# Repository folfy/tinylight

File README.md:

tinylight
=========

USB client for prismatik and tinylight host

Inexpensive USB Light-pack client, based on an Atmel xMega Controller.
Intended for LED Strips based on the WS2801 IC.<br>
<br>
<b>Features:</b>
- On-chip USB interface
- RGB status led
- Supply current and voltage measurement
- 6 GPIO solderpads
- PDI programming interface

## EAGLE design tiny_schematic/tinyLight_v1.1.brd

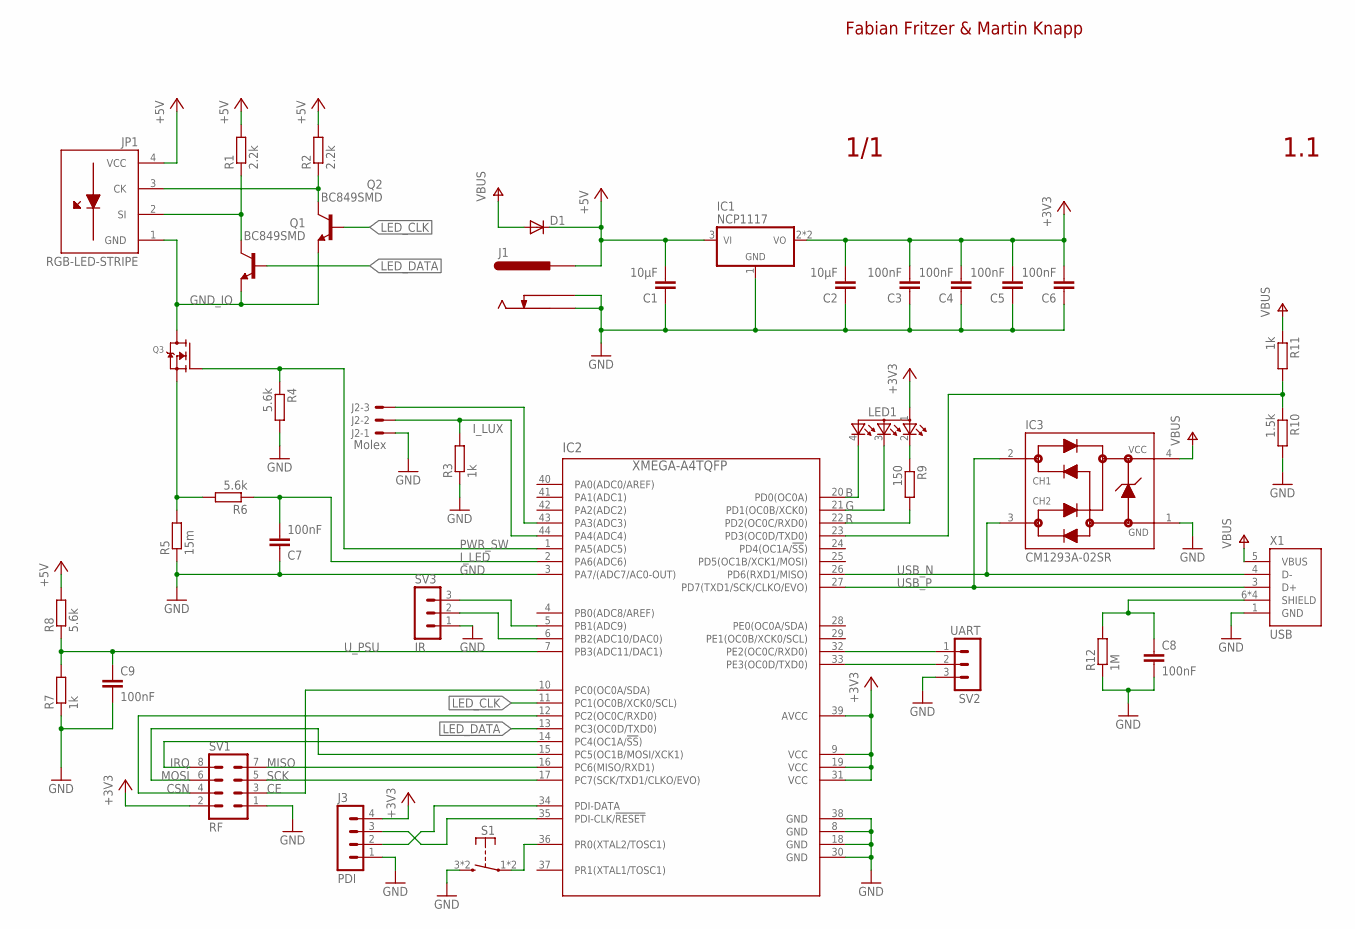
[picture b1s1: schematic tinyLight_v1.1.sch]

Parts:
C1, C2: 10µF; C2012
C3, C4, C5, C6, C7, C8, C9: 100nF; C2012
D1: DIODE-DO-214AC; DO-214AC
IC1: NCP1117; SOT223
IC2: XMEGA-A4TQFP; TQFP44
IC3: CM1293A-02SR; SOT143
J1: RASM722PX
J2: Molex; 6410-03
J3: PDI; MA04-1
JP1: RGB-LED-STRIPE; LED-STRIPE
LED1: RGB-LEDMINI; P-LCC-4_M
Q1, Q2: BC849SMD; SOT23-BEC
Q3: MOSFET-N; SOT457R_PHILIPS
R1, R2: 2.2k; M2012
R3, R7, R11: 1k; M2012
R4, R6, R8: 5.6k; M2012
R5: 15m; M3216
R9: 150; M2012
R10: 1.5k; M2012
R12: 1M; M2012
S1: SPST_PB; LSH_6X6
SV1: RF; MA04-2
SV2: UART; MA03-1
SV3: IR; MA03-1
X1: MICRO-USB; MIKRO_B

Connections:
+3V3: C2.2, C3.2, C4.2, C5.2, C6.2, IC1.2 (VOUT), IC1.T (VOUT), IC2.9 (VCC), IC2.19 (VCC), IC2.31 (VCC), IC2.39 (AVCC), J3.4, LED1.1 (ANODE), SV1.2
+5V: C1.2, D1.C, IC1.3 (VIN), J1.TIP, JP1.4 (VCC), R1.2, R2.2, R8.2
B: IC2.20 (PD0(OC0A)), LED1.4 (CBLUE)
CE: IC2.10 (PC0(OC0A/SDA)), SV1.3
CK: JP1.3 (CK), Q2.C, R2.1
CSN: IC2.12 (PC2(OC0C/RXD0)), SV1.4
DATA: JP1.2 (SI), Q1.C, R1.1
G: IC2.21 (PD1(OC0B/XCK0)), LED1.3 (CGREEN)
GND: C1.1, C2.1, C3.1, C4.1, C5.1, C6.1, C7.1, C8.2, C9.2, IC1.1 (GND), IC2.3 (PA7/(ADC7/AC0-OUT)), IC2.8 (GND), IC2.18 (GND), IC2.30 (GND), IC2.38 (GND), IC3.1 (GND), J1.SHUNT, J1.SLEEVE (SLEVE), J2.1, J3.1, R3.1, R4.2, R5.1, R7.1, R10.2, R12.1, S1.3 (2), S1.4 (2), SV1.1, SV2.3, SV3.1, X1.1 (GND)
GND_IO: JP1.1 (GND), Q1.E, Q2.E, Q3.1 (D), Q3.2 (D), Q3.5 (D), Q3.6 (D)
IRQ: IC2.14 (PC4(OC1A/!SS!)), SV1.8
I_LED: C7.2, IC2.2 (PA6(ADC6)), R6.1
I_LUX: IC2.44 (PA4(ADC4)), J2.2, R3.2
LED_CLK: IC2.11 (PC1(OC0B/XCK0/SCL)), Q2.B
LED_DATA: IC2.13 (PC3(OC0D/TXD0)), Q1.B
LED_R: LED1.2 (CRED), R9.1
MISO: IC2.16 (PC6(MISO/RXD1)), SV1.7
MOSI: IC2.15 (PC5(OC1B/MOSI/XCK1)), SV1.6
unnamed: IC2.6 (PB2(ADC10/DAC0)), SV3.2
unnamed: IC2.43 (PA3(ADC3)), J2.3
unnamed: IC2.33 (PE3(OC0D/TXD0)), SV2.2
unnamed: IC2.32 (PE2(OC0C/RXD0)), SV2.1
unnamed: IC2.36 (PR0(XTAL2/TOSC1)), S1.1, S1.2 (1)
unnamed: IC2.35 (PDI-CLK/!RESET), J3.3
unnamed: IC2.34 (PDI-DATA), J3.2
unnamed: IC2.5 (PB1(ADC9)), SV3.3
PWR_SW: IC2.1 (PA5(ADC5)), Q3.3 (G), R4.1
R: IC2.22 (PD2(OC0C/RXD0)), R9.2
SCK: IC2.17 (PC7(SCK/TXD1/CLKO/EVO)), SV1.5
SHIELD: C8.1, R12.2, X1.6 (SHIELD), X1.7 (SHIELD), X1.8 (SHIELD), X1.9 (SHIELD)
USB_N: IC2.26 (PD6(RXD1/MISO)), IC3.3 (CH2), X1.4 (D-)
USB_P: IC2.27 (PD7(TXD1/SCK/CLKO/EVO)), IC3.2 (CH1), X1.3 (D+)
U_PSU: C9.1, IC2.7 (PB3(ADC11/DAC1)), R7.2, R8.1
VBUS: D1.A, IC3.4 (VCC), R11.1, X1.5 (VBUS)
VBUS_LOW: IC2.23 (PD3(OC0D/TXD0)), R10.1, R11.2
VGND: Q3.4 (S), R5.2, R6.2

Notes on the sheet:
1.1
1/1
Fabian Fritzer & Martin Knapp

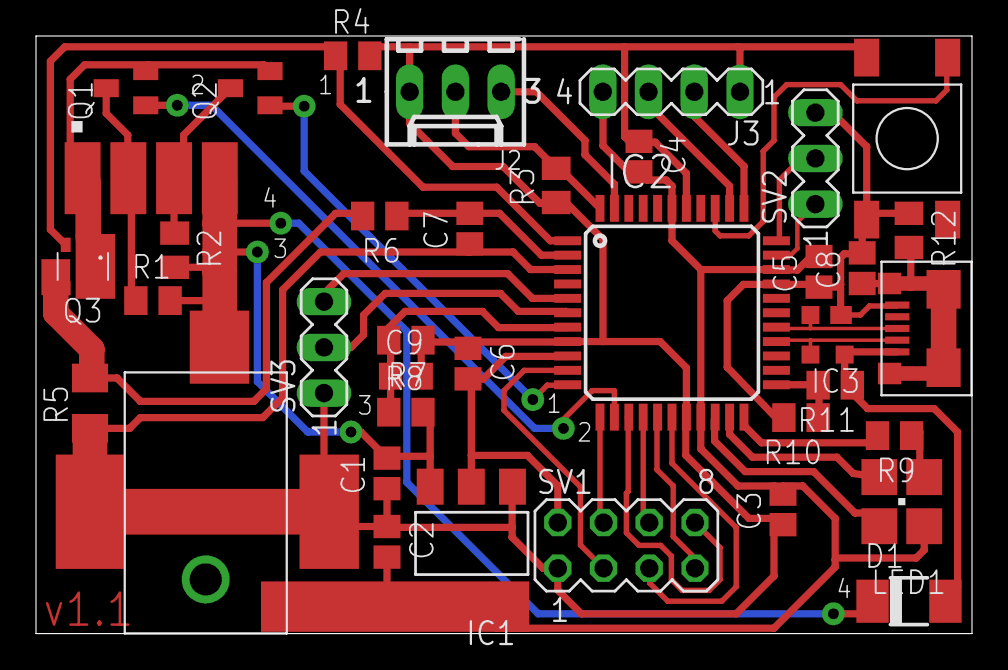
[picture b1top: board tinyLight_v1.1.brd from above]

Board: 2 copper layers, 52.0 x 33.2 mm, 39 parts (0 on the bottom side), 36 nets.

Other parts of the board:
U$1: OSHW_8X100_NOTEXT

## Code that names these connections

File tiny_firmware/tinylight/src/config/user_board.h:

/**
 * \file
 *
 * \brief User board definition template
 *
 * I/O Pins:
 *	PA1:	A_IN:		Light Sensor
 *	PA5:	D_OUT:		Power Mosfet
 *	PA6:	A_IN:		Current-Sensor +
 *	PA7:	A_IN:		Current-Sensor -
 *	PB1:	D_OUT:		IR_enable
 *	PB2:	D_IN:		IR-In
 *	PB3:	A_IN:		+5V-Sensor
 *	PC1:	D_OUT:		XCK-Led Stripe
 *	PC3:	D_OUT:		TX-Led Stripe
 *	PD0:	D_OUT:		Led blue
 *	PD1:	D_OUT:		Led green
 *	PD2:	D_OUT:		Led red
 *	PD3:	D_IN:		USB VBus Detection
 *	PD6:	D_INOUT:	USB Data -
 *	PD7:	D_INOUT:	USB Data +
 *  PE1:    D_OUT:      LED Data - clock (WS2811/WS2812)
 *  PE3:    D_OUT:      LED Data - data  (WS2811/WS2812)
 *	PR3:	D_IN:		Pushbutton
 *
 * Timer/counter units:
 *  TCC0:   LED (WS2811/WS2812)
 *  TCC1:	IR
 *	TCD0:	PWM Status LED
 *	TCD1:	DMA-Wait
 *
 * Event channels:
 *  EVCH0:  ADC
 *  EVCH1:  LED_CLK			(CLK, Falling edge)
 *  EVCH2:  LED_DATA		(DATA, both edges)
 *
 * DMA channels:
 *  DMACH0:	LED Timer
 *  DMACH1: LED Data
 */

 /* This file is intended to contain definitions and configuration details for
 * features and devices that are available on the board, e.g., frequency and
 * startup time for an external crystal, external memory devices, LED and USART
 * pins.
 */

#ifndef USER_BOARD_H
#define USER_BOARD_H

#include <conf_board.h>

//#define BOARD_REV 0x01			//prototype / debug board
//#define BOARD_REV 0x10			//first release
#define BOARD_REV 0x11			//reduced LED pull-up resistor value
/*	uncomment definition to select expected (wireless) module on expansion header	*/
#define RF_avail 1  			//RF-Transceiver
//#define RF_avail 2  			//BT-Transceiver
//#define RF_avail 3  			//Debug Output (remove RF module first!)
//#define UART_avail			//UART-Port
#define DEBUG					//enables reset to bootloader via button

#define SOFTWARE_REV			0x04
#define RTC_TIME				0.02	//20ms
#define BUFFER_SIZE				160

//////////////////////////////////////////////////////////////////////////
/* Internal Hardware */

#ifndef BOARD_REV
#error "BOARD_REV undefined"
#endif

#define DMA_CHANNEL_LED_TIMER	0
#define DMA_CHANNEL_LED			1
#define SLED_TIMER				TCD0
#define SPI_TIMER				TCD1
#define IR_TIMER				TCC1
#define ADC						ADCA

#define ADC_EVCH				4
#define ADC_EVCH_MUX			EVSYS_CH4MUX

#define LED_DATA_EVCH_MUX		EVSYS_CH1MUX
#define LED_DATA_EVCH_CFG		EVSYS_CH1CTRL
#define LED_TRIG_DATA			DMA_CH_TRIGSRC_EVSYS_CH1_gc


#define LED_CLK_EVCH_MUX		EVSYS_CH0MUX
#define LED_CLK_EVCH_CFG		EVSYS_CH0CTRL
#define LED_CLK_EVCH			TC_EVSEL_CH0_gc

//////////////////////////////////////////////////////////////////////////
/* Sens_Light */

#if		BOARD_REV >= 0x10
#define Sens_Light_en			IOPORT_CREATE_PIN(PORTA,3)
#define Sens_Light				IOPORT_CREATE_PIN(PORTA,4)
#define ADCCH_POS_PIN_Light		ADCCH_POS_PIN4
#elif	BOARD_REV == 0x01
#define	Sens_Light				IOPORT_CREATE_PIN(PORTA,1)
#endif

//////////////////////////////////////////////////////////////////////////
/* MOSFET, Sens_I */

#define MOSFET_en				IOPORT_CREATE_PIN(PORTA,5)

#define Sens_I_P				IOPORT_CREATE_PIN(PORTA,6)
#define ADCCH_POS_PIN_Sense		ADCCH_POS_PIN6
#define Sens_I_N				IOPORT_CREATE_PIN(PORTA,7)
#define ADCCH_NEG_PIN_Sense		ADCCH_NEG_PIN7

//////////////////////////////////////////////////////////////////////////
/* IR, Sens_Uin */

#define IR_en					IOPORT_CREATE_PIN(PORTB,2)
#define IR_in					IOPORT_CREATE_PIN(PORTB,1)
#define IR_in_int				PIN1_bm

#define Sens_Uin				IOPORT_CREATE_PIN(PORTB,3)
#define ADCCH_POS_PIN_Volt		ADCCH_POS_PIN11

//////////////////////////////////////////////////////////////////////////
/* LED_USART */

#define LED_WS281X 1

#define	LED_CLK					IOPORT_CREATE_PIN(PORTC,1)
#define	LED_TX					IOPORT_CREATE_PIN(PORTC,3)

#if		LED_WS281X==1
#if		BOARD_REV < 0x11
#warning "For old bords: WS281x requires strong pullup (short LED_CLK and LED_DATA)!"
#endif
#define	LED_XCLK				IOPORT_CREATE_PIN(PORTE,1)
#define LED_XRX					IOPORT_CREATE_PIN(PORTE,2)
#define	LED_XTX					IOPORT_CREATE_PIN(PORTE,3)
#define LED_XCLK_EVMUX			EVSYS_CHMUX_PORTE_PIN1_gc
#define LED_XTX_EVMUX			EVSYS_CHMUX_PORTE_PIN3_gc

#define LED_TC					TCC0
#define LED_TC_CC_REG			TCC0_CCBBUF
#define LED_TC_CC				TC_CCB
#define LED_TC_CCEN				TC_CCBEN

#define LED_USART				USARTE0
#define LED_USART_DATA			USARTE0_DATA
#define LED_USART_DMA_TRIG_DRE	DMA_CH_TRIGSRC_USARTE0_DRE_gc
#else
#define LED_USART				USARTC0
#define LED_USART_DATA			USARTC0_DATA
#define LED_USART_DMA_TRIG_DRE	DMA_CH_TRIGSRC_USARTC0_DRE_gc
#endif

//////////////////////////////////////////////////////////////////////////
/* RF Module */

#if		RF_avail == 1
#define NRF_CE					IOPORT_CREATE_PIN(PORTC,0)
#define NRF_CSN					IOPORT_CREATE_PIN(PORTC,2)
#define NRF_IRQ					IOPORT_CREATE_PIN(PORTC,4)
#define NRF_MOSI				IOPORT_CREATE_PIN(PORTC,5)
#define NRF_MISO				IOPORT_CREATE_PIN(PORTC,6)
#define NRF_SCK					IOPORT_CREATE_PIN(PORTC,7)
#define NRF_SPI					SPIC
#define NRF_SPI_INT_vect		SPIC_INT_vect
#define NRF_INTMSK				PORTC_INT0MASK
#define NRF_INTCTRL				PORTC_INTCTRL
#define NRF_INTLVL				PORT_INT0LVL_LO_gc
#define NRF_INT_vect			PORTC_INT0_vect
#define NRF_IRQ_bm				PIN4_bm

#elif	RF_avail == 2
#define BT_EN					IOPORT_CREATE_PIN(PORTC,0)
#define BT_RX					IOPORT_CREATE_PIN(PORTC,6)
#define BT_TX					IOPORT_CREATE_PIN(PORTC,7)
#define BT_RX_BUFFER_SIZE		32
#define BT_USART				&USARTC1
#define BT_USART_INT_LVL		USART_INT_LVL_LO
#define BT_USART_RX_vect		USARTC1_RXC_vect

#elif	RF_avail == 3
#warning "Debug Output on RF-Header enabled!"
#define set_P3					asm volatile ("sbi 0x11,0");
#define	clr_P3					asm volatile ("cbi 0x11,0");
#define set_P4					asm volatile ("sbi 0x11,2");
#define	clr_P4					asm volatile ("cbi 0x11,2");
#define set_P8					asm volatile ("sbi 0x11,4");
#define	clr_P8					asm volatile ("cbi 0x11,4");
#define set_P6					asm volatile ("sbi 0x11,5");
#define	clr_P6					asm volatile ("cbi 0x11,5");
#define set_P7					asm volatile ("sbi 0x11,6");
#define	clr_P7					asm volatile ("cbi 0x11,6");
#define set_P5					asm volatile ("sbi 0x11,7");
#define	clr_P5					asm volatile ("cbi 0x11,7");
#endif

//////////////////////////////////////////////////////////////////////////
/* SLED */

//		SLED_TIMER
#define SLED_B					IOPORT_CREATE_PIN(PORTD,0)
#define SLED_TC_CC_B			TC_CCA
#define SLED_TC_CCEN_B			TC_CCAEN

#define SLED_G					IOPORT_CREATE_PIN(PORTD,1)
#define SLED_TC_CC_G			TC_CCB
#define SLED_TC_CCEN_G			TC_CCBEN

#define SLED_R					IOPORT_CREATE_PIN(PORTD,2)
#define SLED_TC_CC_R			TC_CCC
#define SLED_TC_CCEN_R			TC_CCCEN

//////////////////////////////////////////////////////////////////////////
/* USB */

#define USB_VBUS				IOPORT_CREATE_PIN(PORTD,3)
#define Vbus_INT_vect			PORTD_INT0_vect
#define VBus_INTMSK				PORTD_INT0MASK
#define VBus_Pin_bm				PIN3_bm

#define USB_D_N					IOPORT_CREATE_PIN(PORTD,6)
#define USB_D_P					IOPORT_CREATE_PIN(PORTD,7)

//////////////////////////////////////////////////////////////////////////
/* Button, UART */

#if		BOARD_REV >= 0x10
#define BUTTON					IOPORT_CREATE_PIN(PORTR,0)
#elif	BOARD_REV == 0x01
#define BUTTON					IOPORT_CREATE_PIN(PORTE,3)
#endif

#ifdef UART_avail
#define UART_RX					IOPORT_CREATE_PIN(PORTE,2)
#define UART_TX					IOPORT_CREATE_PIN(PORTE,3)
#endif

// External oscillator settings.
// Uncomment and set correct values if external oscillator is used.

// External oscillator frequency
//#define BOARD_XOSC_HZ          8000000

// External oscillator type.
//!< External clock signal
//#define BOARD_XOSC_TYPE        XOSC_TYPE_EXTERNAL
//!< 32.768 kHz resonator on TOSC
//#define BOARD_XOSC_TYPE        XOSC_TYPE_32KHZ
//!< 0.4 to 16 MHz resonator on XTALS
//#define BOARD_XOSC_TYPE        XOSC_TYPE_XTAL

// External oscillator startup time
//#define BOARD_XOSC_STARTUP_US  500000


#endif // USER_BOARD_H

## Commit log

2014-04-04 Initial Upload
2014-04-04 Added Uart and Ir-Header
2014-04-04 ignore temp
2014-04-04 Improved clearance, fixed ground routing
2014-04-05 missing firmware upload (bug), added experimental gamma_calc, extended ignore
2014-04-05 header corr
2014-04-06 alternativ mul methode with rounding
2014-04-06 fixed new mode protocol, modified nvm_write, added status_led_off, improved readability
2014-04-06 switch to save_settings()
2014-04-06 synced gamma oversampling
2014-04-07 Revert "switch to save_settings()"
    This reverts commit 927088e2ddb63b11052bca827abe539d1d2756bf.
2014-04-07 added documentation
2014-04-07 fixed usb mode - buffer gamma mapping
2014-04-07 BT Modul added
2014-04-08 Fixed eesave, disabled power down and gamma_calc
2014-04-09 Added IR-Decoder Detection not working
2014-04-10 fixed IR
2014-04-10 fixed gamma_calc, disabled IR
2014-04-11 IR-fixed and working
2014-04-11 Added constants for IR-Remote
2014-04-11 Added EEprom save of Ir colors
2014-04-12 BT-Module finished IR-header moved
2014-04-13 Improved clearance
2014-04-14 close #4
2014-04-15 final board (hopefully...)
2014-04-17 added revision reference, RF net names, fixed cap value
2014-04-17 wrote proper mul16x16 library
2014-04-17 fixed protocol, minor protocol update
2014-04-17 improved portability for future updates
2014-04-17 bugfix, updated protocol_rev, changed cmd_test response
2014-04-17 changed board_rev
2014-04-17 fixed colorswirl, added settings preset, minor improvements
2014-04-18 usb/ada wip
2014-04-18 small corr
2014-04-18 added usb reset
2014-04-18 bootloader ported to new hardware
2014-04-18 usb wip
2014-04-18 rewrote usb
2014-04-20 BT implemented
2014-04-20 dozens of small fixes and improvements, added brownout prevention, adc wip, usb and gamma done
2014-04-20 added new protocol doc (prevent merge problems)
2014-04-21 exported led functions -> led.h
2014-04-21 exported usb functions -> usb lib
2014-04-21 exported settings / sled, misc / adc functions -> set_sled, misc_adc lib
2014-04-22 bugfixes, lib cleanup
2014-04-23 improved formatting
2014-04-23 last changes noted
2014-04-23 completed merge
2014-04-29 inplemented debug tools, reduced adc sample rate, added alpha control, added max value log, removed old error handling, rewrote sled control, fixed ada
2014-04-29 IR fixed and exported
2014-04-29 defined debug tools
2014-04-29 exported bt, fixed ir not avail, removed improper extern declerations
2014-04-30 bugfixes
2014-04-30 bugfix usb drain
2014-04-30 fixed IR, added new single-color-mode, corrected doc
2014-04-30 Defined IR timer in user_board
2014-05-01 Bugfix usb_mode timeout
2014-05-01 Fixed IR again
2014-05-02 BT-layout changed, sleeping status value implemented, IR-alpha implemented
2014-05-18 -(Bugfix) USB Raw mode -Gamma .05 settings resolution -Variable FPS Limit -(Bugfix) Light measurement (x1/2 gain seems to add a big negative offset, hw-bug?)
2014-05-19 Changed IR-pins
2014-05-19 IR pins changed
2014-07-10 BT-driver implemented, fixed count (Not tested)
2014-08-31 RF essentials WIP
2016-03-01 Added comments to schematic; created pdf board documentation
2016-04-04 new board layout added (use usb as alternative power source via diode)
2016-04-04 Migrated to AtmelStudio 7 and ASF 3.21.0; Organized IR-Code (now mandatory); Split global init-file into libs; Moved user_board.h into root-dir (so asf-dir contains no configuration anymore); USB: bu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
2016-04-04 Removed ada-backup; added debug-register; reworked/new sled code (refined blinking)
2016-05-02 *BUGFIXES* (from last two commits)
2016-05-02 introduced folder structure for libraries
2016-05-02 stripped down led usart setup code
2016-05-02 Revert "RF essentials WIP"
    This reverts commit d9e858a75cbe4ba289f600f370b0089ab7043307.
2016-05-02 WS281x support WIP
2016-05-23 ws281x preliminary implementation (test pending)
2016-06-26 Working WS281x implementation (ToDo: Regression Tests)
2016-06-26 minor bugfixes; simplified ADC oversampling
2016-06-28 Minor tweaks, regression bugfixes
2016-06-28 Revert "RF essentials WIP"
    This reverts commit 06b1dd67f1e484136177fc0437bb7ceff5174bc1.
2016-06-28 quick nrf24 test-implementation, but variable payload length is not working yet (bug!)
